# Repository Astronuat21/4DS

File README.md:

Hallo! Welcome to the Github Repository for the 4DS.

4DS is a solo project by Astronuat21 (me!!) aiming to make a dual screen console _akin to the Nintendo DS's_ but with stronger hardware, better battery life and specs in general. The device is also much larger than the ones you might have at home; coming in at around 19x11.5x3cm, the device is better suited for people with bigger hands who may find uncomfortability using even the stardard XL models. The hardware mostly tops the Switch, using the Lattepanda Mu SoC and it's N100 CPU, alongside 16GB of RAM and expandable Gen 3 SSD storage. If you so choose, this project should also be compatible with the upgraded N305 version (although it will be almost useless due to its higher PSU requirements). **NOTE: THIS WILL NOT WORK WITH THE LATTEPANDA MU ULTRA, SINCE IT USES 1.8V I2C and GPIOs.**

This repository contains all the PCB files used in this project, including schematics and circuit boards. **Assuming everything works,** you should be able to reproduce the exact boards I used and reprint them for yourself. Also included are all the 3D files used in 3D printing or other purposes as well as some *outdated -_-* images to look at. They can be found in **/3D Models** and **/Images** respectively. You will also need some of the additional programs included for things like the RP2354 Microcontroller, alongside some other helpful scripts, which can be found in **/Programs**.

I built this to challenge myself to make a console that I would be proud to daily drive. My 2DS XL is great, but it definitely can't play my Steam library, and while I _can_ fit a Switch in some pockets, it dosen't quite have the extensive game library (for what I actually play), the _New (or not really)_ DS in comparison can pretty much play everything before it aside from N64/Gamecube. The Switch needs Nintendo Online (yucky subscription), and that isn't even the full library anyways. 

I may make a v2 using the lattepanda mu ultra, but that thing is like $1000 so... anyone got spare cash?

If you intend to use this repository for any reason, **PLEASE CREDIT ME!!** I am happy to have others use this project as a reference or recreate what I have built, you can contact me with whatever you make, I would be honored. In the future, a _full-ish_ guide will be provided so that you can build your own 4DS if you'd like, but hopefully the repository is clear enough that you can do it on your own.

**DISCLAIMER (yap):** The 4DS and all its files is under the AGPL-3.0 license. I'm therefore technically allowing this repository to used for things like commercial purposes, but trust me, you really don't want to start using this repo just all on your own like that. My warning to you is that _many decisions made here were done from extensive research and considerations from dozens of specifications and datasheets, some areas of this design are much more sensitive than expected, and some areas are not._ I am happy to clarify certain things, but only if I believe your goal is actually good (aka, no AI slop). I'm giving this warning not because you must consult me, but if you choose not to, **find someone to wish you good luck. You're going to need it.**

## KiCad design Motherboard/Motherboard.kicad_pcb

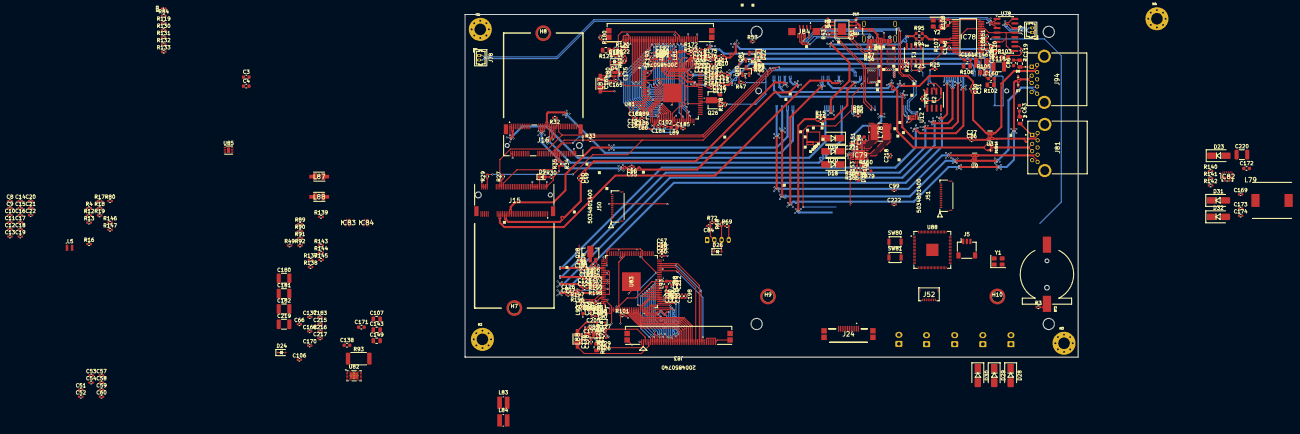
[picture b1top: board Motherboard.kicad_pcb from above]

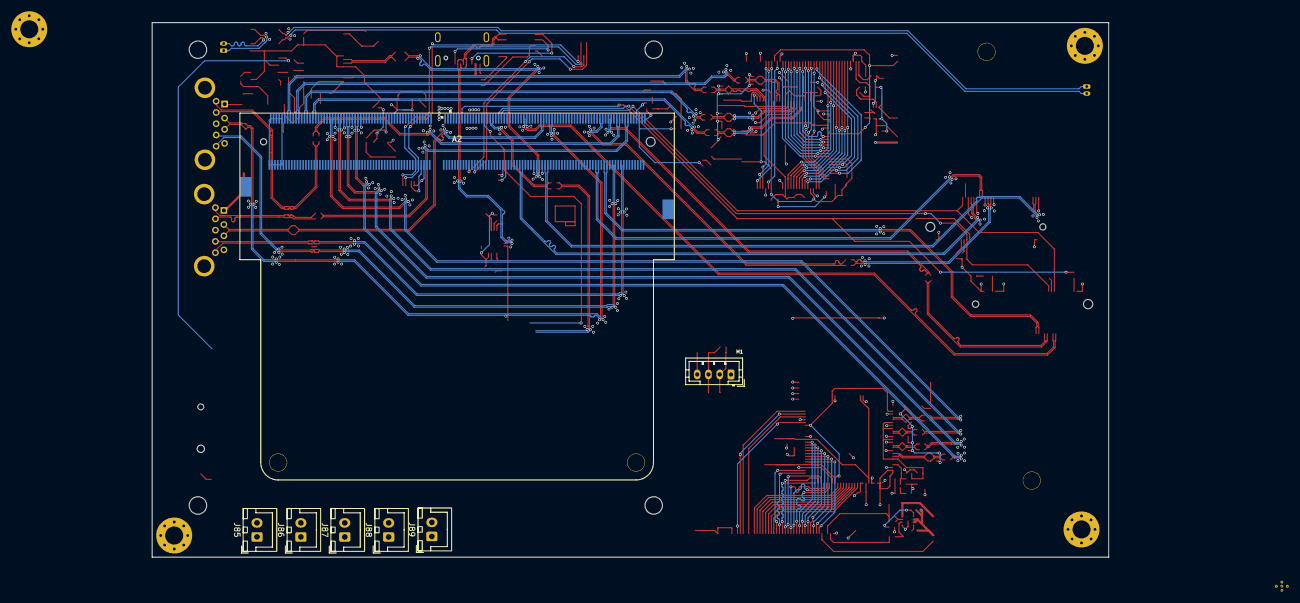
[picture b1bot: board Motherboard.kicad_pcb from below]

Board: 4 copper layers, 170.0 x 95.0 mm, 348 parts (7 on the bottom side), 317 nets.

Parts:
A2: LattePanda_Mu; LattePanda_Module_H8.0mm_Horizontal
BT2: Battery_Cell; Battery_Holder_CR1220_S8411-45R
C3, C4: 15pF; C_0603_1608Metric
C8, C9, C12, C13, C14, C15, C16, C17, C18, C20, C21, C26, C27, C30, C31, C52, C54, C58, C58#2, C60, C60#2, C84: 100nF; C_0402_1005Metric
C10, C11, C19, C22, C99: 4.7uF; C_0402_1005Metric
C49, C50, C55, C56, C169: 220nF; C_0402_1005Metric
C51, C53, C57, C57#2, C59, C59#2, C90, C102, C104, C106, C108, C110, C111, C112, C113, C114, C115, C116, C117, C121, C122, C123, C124, C125, C126, C127, C131, C150, C158, C164, C170, C177, C198, C207, C208, C215, C216, C217, C218, C221, C222: 10uF; C_0402_1005Metric
C61, C66, C119, C120, C128, C137, C147, C148, C151, C165, C166, C176, C179: 1uF; C_0402_1005Metric
C63, C86: 22uF; C_0603_1608Metric
C98: 47nF; C_0603_1608Metric
C107: 10uF; C_0805_2012Metric
C118, C146: 100uF; C_1210_3225Metric
C138: 0.47uF; C_0603_1608Metric
C143, C149: 22uF; C_0805_2012Metric
C160, C161: 0.022uF; C_0603_1608Metric
C168, C183: 1.2nF; C_0402_1005Metric
C171: 100nF; C_0603_1608Metric
C172: 2.2uF; C_0603_1608Metric
C173: 39nF; C_0402_1005Metric
C174: 91pF; C_0402_1005Metric
C175, C178: 10nF; C_0402_1005Metric
C180, C181, C182, C219, C220: 47uF; C_1210_3225Metric
C184, C185, C186, C187, C188, C189, C190, C191, C192, C193, C194, C195, C196, C197, C199, C200, C201, C202, C203, C204, C205, C206, C209, C210, C211, C212, C213, C214: 0.1uF; C_0402_1005Metric
D4, D5, D26: 1N5819WS; D_SOD-323
D7, D8, D10, D11, D15, D16, D21, D33: ESD5V0B03; D_0402_1005Metric
D9, D22, D25: LED_G; LED_0603_1608Metric
D12, D13, D14: PESD24VS1UL-N; D_0402_1005Metric
D18, D19, D20, D23, D28, D29, D30, D31, D32: SS54; D_SMA
D24: B5819WS-TP; D_SOD-323
E1, E2: 24AA025UIDT-I/SN; SOIC8-N_MC_MCH
F4, F6: 6V/2A; Fuse_0805_2012Metric
H1, H2, H3, H4: MountingHole_Pad; MountingHole_3.2mm_M3_Pad_Via
H7, H8: MountingHole_M2.0; MountingHole_3mm_M2_Pad_TopOnly
H9, H10: MountingHole_Pad; MountingHole_3mm_M2_Pad_TopOnly
IC78: PCM2704CDBR; SOP65P780X200-28N
IC79: BQ25606RGER; QFN50P400X400X100-25N-D
IC82: TPS61288LRQQR; PTPS61288RQQR
IC83, IC84: TPS62903RPJR
J5: SM03B-SRSS-TB; JST_SH_SM03B-SRSS-TB_1x03-1MP_P1.00mm_Horizontal
J15: M.2 Socket M; MDT420M03001
J16: M.2 Socket E; MDT420E03001
J24: 200485-0710; 2004850710
J50, J51: 5034801400
J52: 503480-0800; 5034800800
J78: Speaker_L; Molex_PicoBlade_53047-0210_1x02_P1.25mm_Vertical
J79: Speaker_R; Molex_PicoBlade_53047-0210_1x02_P1.25mm_Vertical
J80: USB_C_Receptacle_USB2.0_16P; USB_C_Receptacle_GCT_USB4105-xx-A_16P_TopMnt_Horizontal
J81, J94: GSB311A41EU
J83, J90: 2004850740; CON_2004850740
J84: FFC2A33-08-T-R; FFC2A3308TR
J85: JST_XHP2_Battery1; JST_XH_B2B-XH-A_1x02_P2.50mm_Vertical
J86: JST_XHP2_Battery2; JST_XH_B2B-XH-A_1x02_P2.50mm_Vertical
J87: JST_XHP2_Battery3; JST_XH_B2B-XH-A_1x02_P2.50mm_Vertical
J88: JST_XHP2_Battery4; JST_XH_B2B-XH-A_1x02_P2.50mm_Vertical
J89: JST_XHP2_Battery5; JST_XH_B2B-XH-A_1x02_P2.50mm_Vertical
L5: 3.3uH; L_pol_2016
L78: SRN5030HA-1R0Y; SRN5030HA1R0Y
L79: 7443330220; WE-HCC_109021
L81, L82, L86, L89, L90, L91, L92, L93: BLM18RK601SN1D; L_0603_1608Metric
L83, L84: 74438336010HT
L87, L87#2, L88, L88#2: LQH32CN220K23L; LQH32DN100K23L
M1: Fan_4pin; JST_PH_B4B-PH-K_1x04_P2.00mm_Vertical
Q26, Q28: 2SK3018-TP; SOT-89-3
Q80, Q81: 2N7002; SOT-23
R3, R12, R13, R16, R37, R47: 1k/1%; R_0402_1005Metric
R4, R18, R19, R22, R23, R24, R25, R34, R35, R36, R49, R85, R86, R91, R92, R100, R101, R154: 10k/1%; R_0402_1005Metric
R14, R15: 27R; R_0402_1005Metric
R17: 33R/1%; R_0402_1005Metric
R27, R29, R32, R33: 0R/1%; R_0402_1005Metric
R30, R52, R53, R155: 2.2k/1%; R_0402_1005Metric
R43: 6.8k/1%; R_0402_1005Metric
R46, R48, R69: 100R/1%; R_0402_1005Metric
R51, R80, R138, R144: 100k/1%; R_0402_1005Metric
R68: 21.5K/1%; R_0402_1005Metric
R72: 4.7K/1%; R_0402_1005Metric
R84, R119: 150R/1%; R_0402_1005Metric
R89, R90: 5.1k/1%; R_0402_1005Metric
R93: 0.010R/1%; R_2512_6332Metric
R94, R95: 22R/1%; R_0603_1608Metric
R102, R106: 16R/1%; R_0805_2012Metric
R103, R105: 330R/1%; R_0805_2012Metric
R107: 1.5k/1%; R_0805_2012Metric
R108: 1M/1%; R_0603_1608Metric
R120: 5.1R/1%; R_0402_1005Metric
R121, R122, R127, R128: 910k/1%; R_0402_1005Metric
R123, R126: 5k/1%; R_0402_1005Metric
R124, R125: 90.9k/1%; R_0805_2012Metric
R129: 10R/1%; R_0402_1005Metric
R130, R131, R132, R133: 47R/1%; R_0402_1005Metric
R137, R143: 40.2k/1%; R_0402_1005Metric
R139: 249k/1%; R_0402_1005Metric
R140: 39.2k/1%; R_0402_1005Metric
R141: 931k/1%; R_0402_1005Metric
R142: 48.7k/1%; R_0402_1005Metric
R145: 76.8k/1%; R_0402_1005Metric
R146, R147: 470R/1%; R_0402_1005Metric
R150: 30k/1%; R_0402_1005Metric
R151: 5.24k/1%; R_0402_1005Metric
R152: 226R/1%; R_0402_1005Metric
R153: 169R/1%; R_0402_1005Metric
R166, R167, R168, R169, R172, R173, R175, R176, R196, R197, R198, R199, R202, R203, R205, R206: 56k/1%; R_0402_1005Metric
R178, R208: 21.5k/1%; R_0402_1005Metric
SW80, SW81: SW_Push; SW_SPST_B3U-1000P
TH79: 10k/1%; R_0603_1608Metric
U3, U9, U12: D3V3XA4B10LP-7; Diodes_UDFN-10_1x2.5mm_P0.5mm
U14: CH224K; ESSOP-10-1EP_3.9x5mm_P1.0mm_EP3.2x2.3
U78: PAM8406D; SOIC-16_3.9x9.9mm_P1.27mm
U80, U85, U85#2: PAM2841G; DFN-8-1EP_2x2mm_P0.5mm_EP0.86x1.55mm
U81, U83: TFP401APZP; PZP100_5P2X5P2
U82: BQ27441DRZT-G1A; Texas_S-PDSO-N12
U88: RP2354B; QFN-80-1EP_10x10mm_P0.4mm_EP3.4x3.4mm
Y1, Y2: ABM8-272-T3; Crystal_SMD_3225-4Pin_3.2x2.5mm

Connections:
+1V1: C8.2, C9.2, C10.2, C22.1, L5.2, U88.10 (DVDD), U88.32 (DVDD), U88.51 (DVDD), U88.65 (VREG_FB)
+3V3: C12.2, C13.2, C14.2, C15.2, C16.2, C17.2, C18.2, C19.2, C20.2, C21.2, C51.2, C52.2, C53.2, C54.2, C57.2, C57#2.2, C58.2, C58#2.2, C59.2, C59#2.2, C60.2, C60#2.2, C143.1, C164.2, C165.2, C176.2, C177.2, D25.2 (A), E1.8, E2.8, IC78.7 (VDD), IC78.10 (VBUS), IC78.25 (TEST1), IC78.26 (TEST0), IC78.27 (~SSPND), IC83.3 (VOS), J15.2 (3.3V), J15.4 (3.3V), J15.12 (3.3V), J15.14 (3.3V), J15.16 (3.3V), J15.18 (3.3V), J15.70 (3.3V), J15.72 (3.3V), J15.74 (3.3V), J16.2 (3.3V), J16.4 (3.3V), J16.72 (3.3V), J16.74 (3.3V), J24.2, J50.3, J50.9, J51.3, J51.13, J83.4, J84.3, J90.4, L81.1, L82.1, L83.2, L86.1, L87.1, L87.3, L87#2.1, L87#2.3, L88.1, L88.3, L88#2.1, L88#2.3, L89.1, L90.1, L91.1, L92.1, L93.1, R17.2, R18.1, R19.2, R22.1, R23.2, R24.1, R25.2, R30.2, R34.2, R35.1, R52.2, R89.2, R90.2, R92.2, R100.1, R101.1, R107.1, R138.2, R146.1, R147.1, R154.2, U78.4 (PVDDL), U78.6 (VDD), U78.9 (MODE), U78.13 (PVDDR), U80.2 (VIN), U80.3 (ENA), U81.2 (*PD), U81.3 (ST), U81.7 (*STAG), U81.99 (RSVD), U81.100 (OCK_INV), U83.2 (*PD), U83.3 (ST), U83.7 (*STAG), U83.99 (RSVD), U83.100 (OCK_INV), U85.2 (VIN), U85.3 (ENA), U85#2.2 (VIN), U85#2.3 (ENA), U88.5 (IOVDD), U88.15 (IOVDD), U88.24 (IOVDD), U88.29 (IOVDD), U88.41 (IOVDD), U88.50 (IOVDD), U88.59 (ADC_AVDD), U88.60 (IOVDD), U88.64 (VREG_VIN), U88.68 (USB_OTP_VDD), U88.69 (QSPI_IOVDD), U88.76 (IOVDD)
+5V: C63.2, C84.1, C86.2, C149.1, D26.1 (K), F4.1, F6.1, IC84.3 (VOS), L84.2, M1.2 (+), R72.1, R144.2
+9V: D12.1 (K), D18.2 (A), D19.2 (A), D20.2 (A), J80.A4 (VBUS), J80.A9 (VBUS), J80.B4 (VBUS), J80.B9 (VBUS), R36.1, R37.1
+BATT: A2.115 (VBAT), R3.1
/EXIO/Col1: J50.5, U88.77 (GPIO0)
/EXIO/Col2: J50.11, U88.78 (GPIO1)
/EXIO/Col3: J51.11, U88.38 (GPIO30)
/EXIO/Col4: J51.9, U88.39 (GPIO31)
/EXIO/LED_PWR_B: R131.1, U88.20 (GPIO20)
/EXIO/LED_PWR_G: R132.1, U88.19 (GPIO19)
/EXIO/LED_PWR_R: R119.1, U88.18 (GPIO18)
/EXIO/LED_WiFi_B: R133.1, U88.17 (GPIO17)
/EXIO/LED_WiFi_G: R130.1, U88.16 (GPIO16)
/EXIO/LED_WiFi_R: R84.1, U88.14 (GPIO15)
/EXIO/L_ADC_X: J50.13, U88.52 (GPIO41/ADC1)
/EXIO/L_ADC_Y: J50.12, U88.49 (GPIO40/ADC0)
/EXIO/PWR_Button: D33.1 (A1), J52.1, Q80.1 (G)
/EXIO/RPi_HALL_L: J50.1, U88.80 (GPIO3)
/EXIO/RPi_HALL_R: J51.1, U88.40 (GPIO32)
/EXIO/R_ADC_X: J51.5, U88.54 (GPIO43/ADC3)
/EXIO/R_ADC_Y: J51.6, U88.55 (GPIO44/ADC4)
/EXIO/Row1: J50.4, J51.2, U88.2 (GPIO5)
/EXIO/Row2: J50.7, J51.7, U88.4 (GPIO7)
/EXIO/Row3: J50.2, J51.8, U88.1 (GPIO4)
/EXIO/Row4: J50.6, J51.12, U88.3 (GPIO6)
/EXIO/Row5: J50.14, J51.10, U88.6 (GPIO8)
/EXIO/SL_BRI: J51.14, U88.58 (GPIO47/ADC7)
/EXIO/SL_VOL: J50.8, U88.53 (GPIO42/ADC2)
/Fan_Temp/FAN_1_PWM: A2.2 (FAN1_PWM), R69.1
/Fan_Temp/FAN_1_TAC: A2.4 (FAN1_TAC), R68.2
/LattePanda Module/AMP_L: C120.1, U78.7 (INL)
/LattePanda Module/AMP_R: C119.1, U78.10 (INR)
/LattePanda Module/Audio_D+: A2.76 (USB2_P7+), R94.2
/LattePanda Module/Audio_D-: A2.78 (USB2_P7-), R95.1
/LattePanda Module/Audio_DX+: IC78.9 (D+), R94.1, R107.2
/LattePanda Module/Audio_DX-: IC78.8 (D-), R95.2
/LattePanda Module/DDIB_INT: A2.124 (GPP_F13), J24.9
/LattePanda Module/DDIB_RST: A2.120 (GPP_F15), J24.7
/LattePanda Module/DDIB_TOUCH_SCL: A2.150 (I2C3_SCL), J24.3, U12.5, U12.6 (NC)
/LattePanda Module/DDIB_TOUCH_SDA: A2.152 (I2C3_SDA), J24.5, U12.4, U12.7 (NC)
/LattePanda Module/DDIB_TX0+: A2.217 (DDIB_TX0+), C90.1
/LattePanda Module/DDIB_TX0-: A2.215 (DDIB_TX0-), C121.1
/LattePanda Module/DDIB_TX1+: A2.211 (DDIB_TX1+), C122.1
/LattePanda Module/DDIB_TX1-: A2.209 (DDIB_TX1-), C123.1
/LattePanda Module/DDIB_TX2+: A2.205 (DDIB_TX2+), C124.1
/LattePanda Module/DDIB_TX2-: A2.203 (DDIB_TX2-), C125.1
/LattePanda Module/DDIB_TX3+: A2.199 (DDIB_TX3+), C126.1
/LattePanda Module/DDIB_TX3-: A2.197 (DDIB_TX3-), C127.1
/LattePanda Module/HSIO_0_TX+: A2.13 (HSIO0_TX+), C27.1
/LattePanda Module/HSIO_0_TX-: A2.15 (HSIO0_TX-), C26.1
/LattePanda Module/HSIO_1_TX+: A2.19 (HSIO1_TX+), C31.1
/LattePanda Module/HSIO_1_TX-: A2.21 (HSIO1_TX-), C30.1
/LattePanda Module/HSIO_2_RX+: A2.28 (HSIO2_RX+), J15.43 (PERp0/SATA-B-)
/LattePanda Module/HSIO_2_RX-: A2.30 (HSIO2_RX-), J15.41 (PERn0/SATA-B+)
/LattePanda Module/HSIO_2_TX+: A2.25 (HSIO2_TX+), C49.1
/LattePanda Module/HSIO_2_TX-: A2.27 (HSIO2_TX-), C50.1
/LattePanda Module/HSIO_3_RX+: A2.34 (HSIO3_RX+), J16.41 (PERp0)
/LattePanda Module/HSIO_3_RX-: A2.36 (HSIO3_RX-), J16.43 (PERn0)
/LattePanda Module/HSIO_3_TX+: A2.31 (HSIO3_TX+), C55.1
/LattePanda Module/HSIO_3_TX-: A2.33 (HSIO3_TX-), C56.1
/LattePanda Module/LOUT+: J78.1, U78.1 (+OUT_L)
/LattePanda Module/LOUT-: J78.2, U78.3 (-OUT_L)
/LattePanda Module/REFCLK0+: A2.85 (REFCLK0+), J15.53 (REFCLKn)
/LattePanda Module/REFCLK0-: A2.87 (REFCLK0-), J15.55 (REFCLKp)
/LattePanda Module/REFCLK3+: A2.88 (REFCLK3+), J16.47 (REFCLKp0)
/LattePanda Module/REFCLK3-: A2.90 (REFCLK3-), J16.49 (REFCLKn0)
/LattePanda Module/ROUT+: J79.1, U78.16 (+OUT_R)
/LattePanda Module/ROUT-: J79.2, U78.14 (-OUT_R)
/LattePanda Module/RP+: R14.1, U88.66 (USB_DM)
/LattePanda Module/RP-: R15.1, U88.67 (USB_DP)
/LattePanda Module/RPI_BAT_GPO: A2.118 (GPP_F16), R92.1, U82.12 (GPOUT)
/LattePanda Module/RPI_BAT_SCL: A2.146 (I2C4_SCL), R89.1, U82.1 (SDA)
/LattePanda Module/RPI_BAT_SDA: A2.148 (I2C4_SDA), R90.1, U82.2 (SCL)
/LattePanda Module/RPI_BAT_STAT: IC79.5 (STAT), R154.1, R155.2, U88.46 (GPIO37)
/LattePanda Module/RPR+: A2.111 (USB2_P5+), R14.2
/LattePanda Module/RPR-: A2.109 (USB2_P5-), R15.2
/LattePanda Module/RPi_5A_SCL: R19.1, U88.44 (GPIO35)
/LattePanda Module/RPi_5A_SDA: R18.2, U88.43 (GPIO34)
/LattePanda Module/RPi_LCD_EN: J83.31, J90.31, R100.2, R101.2, U81.8 (SCDT), U81.9 (*PDO), U83.8 (SCDT), U83.9 (*PDO), U88.79 (GPIO2)
/LattePanda Module/RPi_PAM_LPWR: U78.5 (~MUTE), U88.25 (GPIO24)
/LattePanda Module/SLS_S3: A2.7 (SLS_S3), R46.1, U88.36 (GPIO28)
/LattePanda Module/SUSCLK_WIFI: A2.131 (SUSCLK), R29.2, R33.2
/LattePanda Module/SWCLK: J5.1, U88.33 (SWCLK)
/LattePanda Module/SWD: J5.3, U88.34 (SWDIO)
/LattePanda Module/TCP0_INT: A2.126 (GPP_F12), J84.6
/LattePanda Module/TCP0_RST: A2.122 (GPP_F14), J84.7
/LattePanda Module/TCP0_TOUCH_SCL: A2.154 (I2C2_SCL), J84.4, U12.2, U12.9 (NC)
/LattePanda Module/TCP0_TOUCH_SDA: A2.156 (I2C2_SDA), J84.5, U12.1, U12.10 (NC)
/LattePanda Module/TCP0_TX0+: A2.247 (TCP0_TX0+), C110.1
/LattePanda Module/TCP0_TX0-: A2.245 (TCP0_TX0-), C111.1
/LattePanda Module/TCP0_TX1+: A2.241 (TCP0_TXRX0+), C112.1
/LattePanda Module/TCP0_TX1-: A2.239 (TCP0_TXRX0-), C113.1
/LattePanda Module/TCP0_TX2+: A2.235 (TCP0_TX1+), C114.1
/LattePanda Module/TCP0_TX2-: A2.233 (TCP0_TX1-), C115.1
/LattePanda Module/TCP0_TX3+: A2.229 (TCP0_TXRX1+), C116.1
/LattePanda Module/TCP0_TX3-: A2.227 (TCP0_TXRX1-), C117.1
/LattePanda Module/USB_2_P7+: A2.70 (USB2_P4+), J16.3 (USB_D+)
/LattePanda Module/USB_2_P7-: A2.72 (USB2_P4-), J16.5 (USB_D-)
/LattePanda Module/WiFi_M2E_LED: J16.6 (~LED_1), U88.56 (GPIO45/ADC5)
/LattePanda Module/~PWR_SW: A2.1 (~PWRBTN), R48.2
/LattePanda Module/~USB_BOOT: R16.1, SW81.1
/M.2 E&M Key/CON_PCIE_TX_0+: C55.2, J16.35 (PETp0)
/M.2 E&M Key/CON_PCIE_TX_0-: C56.2, J16.37 (PETn0)
/M.2 E&M Key/CON_PCIE_TX_1+: C49.2, J15.49 (PETp0/SATA-A+)
/M.2 E&M Key/CON_PCIE_TX_1-: C50.2, J15.47 (PETn0/SATA-A-)
/M.2 E&M Key/~CLKREQE: J16.53 (~CLKREQ0), R32.1
/M.2 E&M Key/~CLKREQM: J15.52 (~CLKREQ), R27.1
/PSU/12VIn: C220.2, D23.2 (A), D31.2 (A), D32.2 (A), IC82.5 (VOUT), IC82.13 (VOUT), R141.2
/PSU/BAT+: C222.1, D28.1 (K), D29.1 (K), D30.1 (K), IC79.13 (BAT_1), IC79.14 (BAT_2)
/PSU/B_RAW: C137.2, J85.2, J86.2, J87.2, J88.2, J89.2, R93.2, U82.6 (BAT), U82.8 (SRP)
/PSU/CC1: D13.1 (K), J80.A5 (CC1), U14.7 (CC1)
/PSU/CC2: D14.1 (K), J80.B5 (CC2), U14.6 (CC2)
/PSU/PWR_C_D+: D11.2 (A2), IC79.3 (D+), J80.A6 (D+), J80.B6 (D+), U14.4 (DP)
/PSU/PWR_C_D-: D10.2 (A2), IC79.4 (D-), J80.A7 (D-), J80.B7 (D-), U14.5 (DM)
/PSU/SYS: C106.1, C170.1, C171.2, C215.1, C216.1, C217.1, C218.1, IC79.15 (SYS_1), IC79.16 (SYS_2), IC82.6 (EN), IC82.7 (VIN), IC82.14 (VIN), IC83.5 (EN), IC83.6 (VIN), L78.2, L79.1
/RGB/B0: J83.5, U83.30 (QE16)
/RGB/B1: J83.6, U83.31 (QE17)
/RGB/B2: J83.7, U83.32 (QE18)
/RGB/B3: J83.8, U83.33 (QE19)
/RGB/B4: J83.9, U83.34 (QE20)
/RGB/B5: J83.10, U83.35 (QE21)
/RGB/B6: J83.11, U83.36 (QE22)
/RGB/B7: J83.12, U83.37 (QE23)
/RGB/B8: J83.13, U83.20 (QE8)
/RGB/B9: J83.14, U83.21 (QE9)
/RGB/B10: J83.15, U83.22 (QE10)
/RGB/B11: J83.16, U83.23 (QE11)
/RGB/B12: J83.17, U83.24 (QE12)
/RGB/B13: J83.18, U83.25 (QE13)
/RGB/B14: J83.19, U83.26 (QE14)
/RGB/B15: J83.20, U83.27 (QE15)
/RGB/B16: J83.21, U83.10 (QE0)
/RGB/B17: J83.22, U83.11 (QE1)
/RGB/B18: J83.23, U83.12 (QE2)
/RGB/B19: J83.24, U83.13 (QE3)
/RGB/B20: J83.25, U83.14 (QE4)
/RGB/B21: J83.26, U83.15 (QE5)
/RGB/B22: J83.27, U83.16 (QE6)
/RGB/B23: J83.28, U83.17 (QE7)
/RGB/B-AVDD: C207.2, C209.1, C211.1, C213.1, C214.1, L92.2, U83.82 (AVDD), U83.84 (AVDD), U83.88 (AVDD), U83.95 (AVDD)
/RGB/B-DE: J83.30, U83.46 (DE)
/RGB/B-DVDD: C208.2, C210.1, C212.1, L93.2, U83.6 (DVDD), U83.38 (DVDD), U83.67 (DVDD)
/RGB/B-HS: J83.32, U83.48 (HSYNC)
/RGB/B-OVDD: C198.2, C200.1, C202.1, C204.1, C206.1, L91.2, U83.18 (OVDD), U83.29 (OVDD), U83.43 (OVDD), U83.57 (OVDD), U83.78 (OVDD)
/RGB/B-PCK: J83.34, U83.44 (ODCK)
/RGB/B-PVDD: C158.2, C199.1, C201.1, C203.1, C205.1, L90.2, U83.97 (PVDD)
/RGB/B-VS: J83.33, U83.47 (VSYNC)
/RGB/DDIB_CK+: C126.2, R197.1, U83.93 (RXC+)
/RGB/DDIB_CK-: C127.2, R196.1, U83.94 (RXC-)
/RGB/DDIB_D0+: C124.2, R199.1, U83.90 (RX0+)
/RGB/DDIB_D0-: C125.2, R198.1, U83.91 (RX0-)
/RGB/DDIB_D1+: C122.2, R203.1, U83.85 (RX1+)
/RGB/DDIB_D1-: C123.2, R202.1, U83.86 (RX1-)
/RGB/DDIB_D2+: C90.2, R206.1, U83.80 (RX2+)
/RGB/DDIB_D2-: C121.2, R205.1, U83.81 (RX2-)
/RGB/P0: J90.5, U81.30 (QE16)
/RGB/P1: J90.6, U81.31 (QE17)
/RGB/P2: J90.7, U81.32 (QE18)
/RGB/P3: J90.8, U81.33 (QE19)
/RGB/P4: J90.9, U81.34 (QE20)
/RGB/P5: J90.10, U81.35 (QE21)
/RGB/P6: J90.11, U81.36 (QE22)
/RGB/P7: J90.12, U81.37 (QE23)
/RGB/P8: J90.13, U81.20 (QE8)
/RGB/P9: J90.14, U81.21 (QE9)
/RGB/P10: J90.15, U81.22 (QE10)
/RGB/P11: J90.16, U81.23 (QE11)
/RGB/P12: J90.17, U81.24 (QE12)
/RGB/P13: J90.18, U81.25 (QE13)
/RGB/P14: J90.19, U81.26 (QE14)
/RGB/P15: J90.20, U81.27 (QE15)
/RGB/P16: J90.21, U81.10 (QE0)
/RGB/P17: J90.22, U81.11 (QE1)
/RGB/P18: J90.23, U81.12 (QE2)
/RGB/P19: J90.24, U81.13 (QE3)
/RGB/P20: J90.25, U81.14 (QE4)
/RGB/P21: J90.26, U81.15 (QE5)
/RGB/P22: J90.27, U81.16 (QE6)
/RGB/P23: J90.28, U81.17 (QE7)
/RGB/P-AVDD: C131.2, C194.1, C195.1, C196.1, C197.1, L81.2, U81.82 (AVDD), U81.84 (AVDD), U81.88 (AVDD), U81.95 (AVDD)
/RGB/P-DE: J90.34, U81.46 (DE)
/RGB/P-DVDD: C102.2, C184.1, C185.1, L89.2, U81.6 (DVDD), U81.38 (DVDD), U81.67 (DVDD)
/RGB/P-HS: J90.32, U81.48 (HSYNC)
/RGB/P-OVDD: C104.2, C186.1, C187.1, C188.1, C189.1, L86.2, U81.18 (OVDD), U81.29 (OVDD), U81.43 (OVDD), U81.57 (OVDD), U81.78 (OVDD)
/RGB/P-PCK: J90.30, U81.44 (ODCK)
/RGB/P-PVDD: C108.2, C190.1, C191.1, C192.1, C193.1, L82.2, U81.97 (PVDD)
/RGB/P-VS: J90.33, U81.47 (VSYNC)
/RGB/TMDS_CK+: C116.2, R167.1, U81.93 (RXC+)
/RGB/TMDS_CK-: C117.2, R166.1, U81.94 (RXC-)
/RGB/TMDS_D0+: C114.2, R169.1, U81.90 (RX0+)
/RGB/TMDS_D0-: C115.2, R168.1, U81.91 (RX0-)
/RGB/TMDS_D1+: C112.2, R173.1, U81.85 (RX1+)
/RGB/TMDS_D1-: C113.2, R172.1, U81.86 (RX1-)
/RGB/TMDS_D2+: C110.2, R176.1, U81.80 (RX2+)
/RGB/TMDS_D2-: C111.2, R175.1, U81.81 (RX2-)
/USB/CON_USB3_D_N: A2.73 (USB2_P2-), D16.2 (A2), J81.2 (D-)
/USB/CON_USB3_D_P: A2.75 (USB2_P2+), D15.2 (A2), J81.3 (D+)
/USB/CON_USB3_SSRX_N: A2.18 (HSIO0_RX-), J81.5 (STDA_SSRX-), U9.4, U9.7 (NC)
/USB/CON_USB3_SSRX_P: A2.16 (HSIO0_RX+), J81.6 (STDA_SSRX+), U9.5, U9.6 (NC)
/USB/CON_USB3_SSTX_N: C26.2, J81.8 (STDA_SSTX-), U3.1, U3.10 (NC)
/USB/CON_USB3_SSTX_P: C27.2, J81.9 (STDA_SSTX+), U3.2, U3.9 (NC)
/USB/CON_USB4_D_N: A2.67 (USB2_P1-), D8.2 (A2), J94.2 (D-)
/USB/CON_USB4_D_P: A2.69 (USB2_P1+), D7.2 (A2), J94.3 (D+)
/USB/CON_USB4_SSRX_N: A2.24 (HSIO1_RX-), J94.5 (STDA_SSRX-), U9.1, U9.10 (NC)
/USB/CON_USB4_SSRX_P: A2.22 (HSIO1_RX+), J94.6 (STDA_SSRX+), U9.2, U9.9 (NC)
/USB/CON_USB4_SSTX_N: C30.2, J94.8 (STDA_SSTX-), U3.4, U3.7 (NC)
/USB/CON_USB4_SSTX_P: C31.2, J94.9 (STDA_SSTX+), U3.5, U3.6 (NC)
/~PLT_RST: A2.105 (~PLTRST), J15.50 (~PERST), J16.52 (~PERST0)
/~PWR_LED/~PSON: A2.5 (SLS_S0), R47.1, R178.1, R208.1, U88.37 (GPIO29)
/~WAKE: A2.103 (~WAKE), J15.54 (~PEWAKE), J16.55 (~PEWAKE0)
GND: A2.11 (GND), A2.14 (GND), A2.17 (GND), A2.20 (GND), A2.23 (GND), A2.26 (GND), A2.29 (GND), A2.32 (GND), A2.35 (GND), A2.38 (GND), A2.41 (GND), A2.44 (GND), A2.47 (GND), A2.50 (GND), A2.53 (GND), A2.56 (GND), A2.59 (GND), A2.62 (GND), A2.65 (GND), A2.68 (GND), A2.71 (GND), A2.74 (GND), A2.77 (GND), A2.80 (GND), A2.83 (GND), A2.86 (GND), A2.89 (GND), A2.92 (GND), A2.95 (GND), A2.98 (GND), A2.101 (GND), A2.107 (GND), A2.110 (GND), A2.113 (GND), A2.116 (GND), A2.135 (GND), A2.136 (GND), A2.151 (GND), A2.158 (GND), A2.167 (GND), A2.170 (GND), A2.181 (GND), A2.182 (GND), A2.188 (GND), A2.189 (GND), A2.194 (GND), A2.195 (GND), A2.200 (GND), A2.201 (GND), A2.206 (GND), A2.207 (GND), A2.212 (GND), A2.213 (GND), A2.218 (GND), A2.219 (GND), A2.224 (GND), A2.225 (GND), A2.230 (GND), A2.231 (GND), A2.236 (GND), A2.237 (GND), A2.242 (GND), A2.243 (GND), A2.248 (GND), A2.249 (GND), A2.MP (Mountinge_Pads), BT2.2 (-), C3.1, C4.1, C8.1, C9.1, C10.1, C11.1, C12.1, C13.1, C14.1, C15.1, C16.1, C17.1, C18.1, C19.1, C20.1, C21.1, C22.2, C51.1, C52.1, C53.1, C54.1, C57.1, C57#2.1, C58.1, C58#2.1, C59.1, C59#2.1, C60.1, C60#2.1, C61.2, C63.1, C66.2, C84.2, C86.1, C99.2, C102.1, C104.1, C106.2, C107.2, C108.1, C128.1, C131.1, C137.1, C138.1, C143.2, C147.2, C148.2, C150.2, C151.2, C158.1, C165.1, C168.1, C170.2, C171.1, C172.2, C173.1, C174.1, C175.1, C176.1, C178.1, C180.1, C181.1, C182.1, C183.1, C184.2, C185.2, C186.2, C187.2, C188.2, C189.2, C190.2, C191.2, C192.2, C193.2, C194.2, C195.2, C196.2, C197.2, C198.1, C199.2, C200.2, C201.2, C202.2, C203.2, C204.2, C205.2, C206.2, C207.1, C208.1, C209.2, C210.2, C211.2, C212.2, C213.2, C214.2, C215.2, C216.2, C217.2, C218.2, C219.1, C220.1, C221.2, C222.2, D7.1 (A1), D8.1 (A1), D10.1 (A1), D11.1 (A1), D12.2 (A), D13.2 (A), D14.2 (A), D15.1 (A1), D16.1 (A1), D21.1 (A1), D24.2 (A), D33.2 (A2), E1.1, E1.2, E1.3, E1.4, E2.1, E2.2, E2.3, E2.4, H1.1 (1_1), H2.1 (1_1), H3.1 (1_1), H4.1 (1_1), H7.1 (1_1), H8.1 (1_1), H9.1 (1_1), H10.1 (1_1), IC78.4 (PSEL), IC78.6 (DGND), IC78.11 (ZGND), IC78.12 (AGNDL), IC78.17 (AGNDR), IC78.19 (PGND), IC78.21 (HOST), IC78.22 (HID0/MS), IC78.23 (HID1/MC), IC78.24 (HID2/MD), IC79.6 (OTG), IC79.9 (~CE), IC79.17 (GND_1), IC79.18 (GND_2), IC79.25 (EP), IC82.3 (PGND), IC82.10 (AGND), IC82.12 (PGND), IC83.4 (GND), IC84.4 (GND), J5.2, J5.MP (MountPin), J15.1 (GND), J15.3 (GND), J15.9 (GND), J15.15 (GND), J15.21 (GND), J15.27 (GND), J15.33 (GND), J15.39 (GND), J15.45 (GND), J15.51 (GND), J15.57 (GND), J15.71 (GND), J15.73 (GND), J15.75 (GND), J15.MP1, J15.MP2, J16.1 (GND), J16.7 (GND), J16.18 (GND), J16.33 (GND), J16.39 (GND), J16.45 (GND), J16.51 (GND), J16.57 (GND), J16.63 (GND), J16.69 (GND), J16.75 (GND), J16.MP1, J16.MP2, J24.1, J24.10, J24.G1 (GND_1), J24.G2 (GND_2), J24.MP1, J24.MP2, J24.MP3, J24.MP4, J50.10, J50.P1, J50.P2, J51.4, J51.P1, J51.P2, J52.2, J52.9, J52.10, J80.A1 (GND), J80.A12 (GND), J80.B1 (GND), J80.B12 (GND), J80.SH (SHIELD), J81.4 (GND), J81.7 (GND_DRAIN), J81.MH1, J81.MH2, J83.3, J83.29, J83.36, J83.G1, J83.G2, J83.P1, J83.P2, J83.P3, J83.P4, J84.1, J84.8, J84.MP1, J84.MP2, J85.1, J86.1, J87.1, J88.1, J89.1, J90.3, J90.29, J90.36, J90.G1, J90.G2, J90.P1, J90.P2, J90.P3, J90.P4, J94.4 (GND), J94.7 (GND_DRAIN), J94.MH1, J94.MH2, M1.1 (-), Q26.2 (S), Q28.2 (S), Q80.2 (S), Q81.2 (S), R13.1, R27.2, R32.2, R43.2, R49.1, R51.1, R80.2, R85.2, R86.2, R91.1, R102.2, R103.1, R105.1, R106.2, R120.1, R122.1, R124.2, R125.2, R128.1, R129.1, R137.2, R139.1, R142.1, R143.2, R150.2, R152.2, R153.1, SW81.2, TH79.1, U3.3 (VSS), U3.8 (VSS), U9.3 (VSS), U9.8 (VSS), U12.3 (VSS), U12.8 (VSS), U14.0 (GND), U78.2 (PGNDL), U78.11 (GND), U78.15 (PGNDR), U80.5 (GND), U80.9 (GND), U81.1 (DFO), U81.4 (PIXS), U81.5 (GND), U81.19 (OGND), U81.28 (OGND), U81.39 (GND), U81.45 (OGND), U81.58 (OGND), U81.68 (GND), U81.76 (OGND), U81.79 (AGND), U81.83 (AGND), U81.87 (AGND), U81.89 (AGND), U81.92 (AGND), U81.98 (PGND), U81.PAD, U82.3 (V_{SS}), U82.13 (PAD), U83.1 (DFO), U83.4 (PIXS), U83.5 (GND), U83.19 (OGND), U83.28 (OGND), U83.39 (GND), U83.45 (OGND), U83.58 (OGND), U83.68 (GND), U83.76 (OGND), U83.79 (AGND), U83.83 (AGND), U83.87 (AGND), U83.89 (AGND), U83.92 (AGND), U83.98 (PGND), U83.PAD, U85.5 (GND), U85.9 (GND), U85#2.5 (GND), U85#2.9 (GND), U88.62 (VREG_PGND)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
LED_SCB+: C179.2, D5.1 (K), J83.2, R127.2
LED_SCB-: J83.1, R126.1, R129.2
LED_SCT+: C166.2, D4.1 (K), J90.2, R121.2
LED_SCT-: J90.1, R120.2, R123.1
unnamed: A2.171 (DDIB_DDC_SCL), E1.6, R23.1
unnamed: A2.169 (DDIB_DDC_SDA), E1.5, R22.2
unnamed: A2.183 (DDIB_HPD), R147.2
unnamed: A2.179 (TCP0_DDC_SCL), E2.6, R25.1
unnamed: A2.177 (TCP0_DDC_SDA), E2.5, R24.2
unnamed: A2.187 (TCP0_HPD), R146.2
unnamed: A2.185 (TCP1_HPD), R80.1
unnamed: A2.133 (~BIOS_SEL), R4.1
unnamed: A2.100 (~CLKREQ3), R86.1
unnamed: A2.102 (~CLKREQ4), R85.1
unnamed: BT2.1 (+), R3.2
unnamed: C4.2, R12.1, Y1.3
unnamed: C118.2, C119.2, R103.2
unnamed: C120.2, C146.2, R105.2
unnamed: C149.2, R145.1
unnamed: C160.2, R102.1
unnamed: C161.2, R106.1
unnamed: C169.2, IC82.4 (SW), IC82.9 (SW), L79.2
unnamed: C173.2, R140.2
unnamed: D4.2 (A), L87.2, L87.4, L87#2.2, L87#2.4, U80.8 (SW)
unnamed: D5.2 (A), L88.2, L88.4, L88#2.2, L88#2.4, U85.8 (SW), U85#2.8 (SW)
unnamed: D9.2 (A), R30.1
unnamed: D9.1 (K), J15.10 (DAS/~DSS/~LED1)
unnamed: D18.1 (K), D19.1 (K), D20.1 (K), IC79.1 (VAC), IC79.24 (VBUS)
unnamed: D22.2 (A), R52.1
unnamed: D22.1 (K), Q81.3 (D)
unnamed: D25.1 (K), R155.1
unnamed: D26.2 (A), M1.3 (Tacho), R68.1, R72.2
unnamed: D28.2 (A), D29.2 (A), D30.2 (A), R93.1, U82.7 (SRN)
unnamed: C148.1, IC78.13 (VCCL)
unnamed: C151.1, IC78.20 (VCCP)
unnamed: C147.1, IC78.16 (VCCR)
unnamed: C150.1, IC78.18 (VCOM)
unnamed: C146.1, C161.1, IC78.14 (VOUTL)
unnamed: C118.1, C160.1, IC78.15 (VOUTR)
unnamed: IC78.28 (XTI), R108.2, Y2.1
unnamed: IC78.1 (XTO), R108.1, Y2.3
unnamed: C98.2, IC79.21 (BTST)
unnamed: IC79.10 (ICHG), R152.1
unnamed: IC79.8 (ILIM), R153.2
unnamed: C221.1, IC79.23 (PMID)
unnamed: C99.1, IC79.22 (REGN), R151.1
unnamed: C98.1, IC79.19 (SW_1), IC79.20 (SW_2), L78.1
unnamed: IC79.11 (TS), R150.1, R151.2, TH79.2
unnamed: C169.1, IC82.8 (BST)
unnamed: C174.2, IC82.2 (COMP), R140.1
unnamed: IC82.1 (FB), IC82.15 (FB), R141.1, R142.2
unnamed: C172.1, IC82.11 (VCC)
unnamed: IC83.9 (FB/VSET), R139.2
unnamed: IC83.7 (MODE/S-CONF), R137.1
unnamed: IC83.1 (PG), R138.1
unnamed: C168.2, IC83.8 (SS/TR)
unnamed: IC83.2 (SW), L83.1
unnamed: IC84.9 (FB/VSET), R145.2
unnamed: IC84.7 (MODE/S-CONF), R143.1
unnamed: IC84.1 (PG), R144.1
unnamed: C183.2, IC84.8 (SS/TR)
unnamed: IC84.2 (SW), L84.1
unnamed: J15.68 (SUSCLK), R29.1
unnamed: J16.50 (SUSCLK), R33.1
unnamed: J16.56 (~W_DISABLE1), R34.1
unnamed: J16.54 (~W_DISABLE2), R35.2
unnamed: J52.3, R84.2
unnamed: J52.4, R130.2
unnamed: J52.5, R133.2
unnamed: J52.6, R119.2
unnamed: J52.7, R132.2
unnamed: J52.8, R131.2
unnamed: F4.2, J81.1 (VBUS)
unnamed: F6.2, J94.1 (VBUS)
unnamed: M1.4 (PWM), R69.2
unnamed: Q26.3 (D), R166.2, R167.2, R168.2, R169.2, R172.2, R173.2, R175.2, R176.2
unnamed: Q26.1 (G), R178.2
unnamed: Q28.3 (D), R196.2, R197.2, R198.2, R199.2, R202.2, R203.2, R205.2, R206.2
unnamed: Q28.1 (G), R208.2
unnamed: Q81.1 (G), R47.2, R49.2
unnamed: R13.2, SW80.1
unnamed: R46.2, R51.2
unnamed: R43.1, U14.9 (CFG1)
unnamed: R36.2, U14.8 (VBUS)
unnamed: C61.1, R37.2, U14.1 (VDD)
unnamed: C128.2, U78.8 (VREF)
unnamed: C175.2, U80.4 (Comp)
unnamed: R123.2, R124.1, U80.6 (FB)
unnamed: R121.1, R122.2, U80.7 (OVP)
unnamed: R91.2, U82.10 (BIN)
unnamed: C138.2, U82.5 (V_{DD})
unnamed: C178.2, U85.4 (Comp), U85#2.4 (Comp)
unnamed: R125.1, R126.2, U85.6 (FB), U85#2.6 (FB)
unnamed: R127.1, R128.2, U85.7 (OVP), U85#2.7 (OVP)
unnamed: SW80.2, U88.35 (RUN)
unnamed: C11.2, R17.1, U88.61 (VREG_AVDD)
unnamed: L5.1, U88.63 (VREG_LX)
unnamed: C3.2, U88.30 (XIN), Y1.1
unnamed: R12.2, U88.31 (XOUT)
unnamed: R16.2, U88.75 (~QSPI_SS)
PGND_B: C177.1, C179.1, U85.1 (PGND), U85#2.1 (PGND)
PGND_T: C164.1, C166.1, U80.1 (PGND)
PWR: C66.1, D21.2 (A2), Q80.3 (D), R48.1
VDC: A2.250 (VIN), A2.251 (VIN), A2.252 (VIN), A2.253 (VIN), A2.254 (VIN), A2.255 (VIN), A2.256 (VIN), A2.257 (VIN), A2.258 (VIN), A2.259 (VIN), A2.260 (VIN), C107.1, C180.2, C181.2, C182.2, C219.2, D23.1 (K), D31.1 (K), D32.1 (K), IC84.5 (EN), IC84.6 (VIN), R53.1
VPullup: D24.1 (K), R4.2, R53.2

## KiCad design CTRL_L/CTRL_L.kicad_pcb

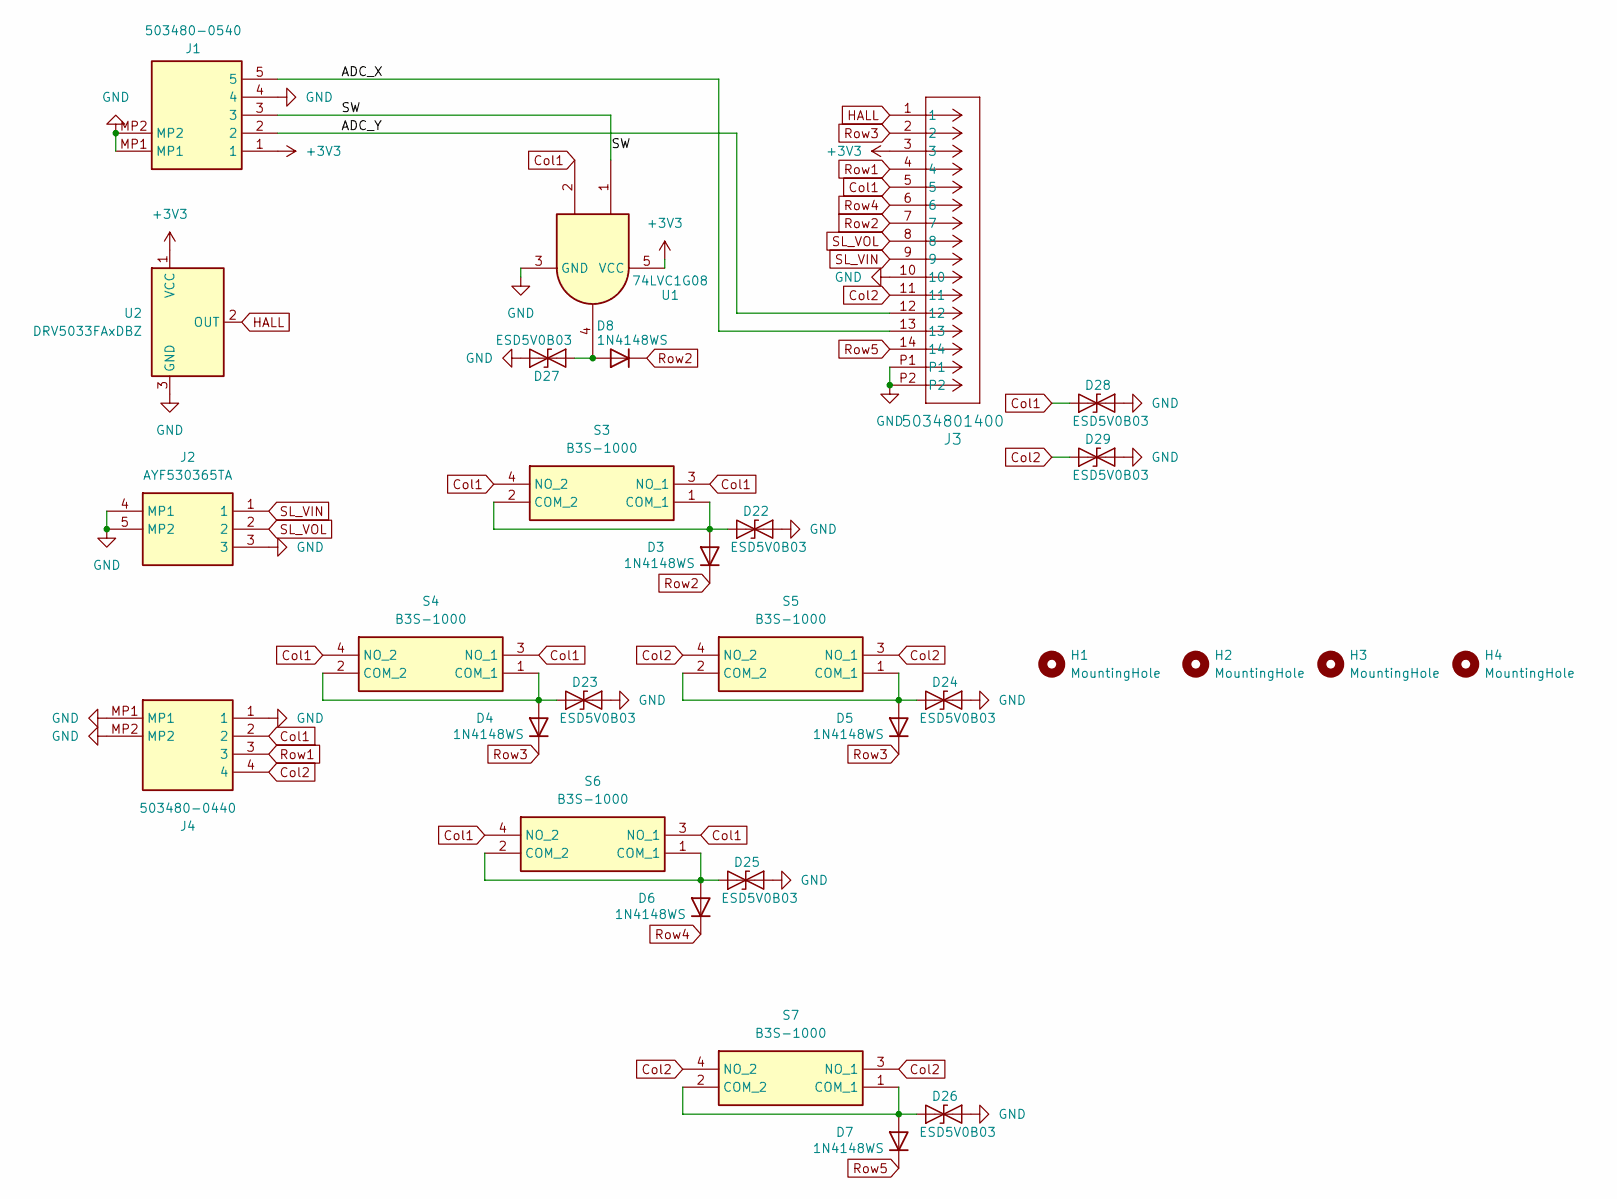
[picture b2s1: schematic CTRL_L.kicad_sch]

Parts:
D3, D4, D5, D6, D7, D8: 1N4148WS; D_SOD-323; MPN 1N4148WS; LCSC Part C917117
D22, D23, D24, D25, D26, D27, D28, D29: ESD5V0B03; D_0402_1005Metric; MPN ESD5V0B03-1006; LCSC Part C521894
H1, H2, H3, H4: MountingHole; MountingHole_2.7mm_M2.5; LCSC Part N/A
J1: 503480-0540; 5034800540; Mouser Part Number 538-503480-0540
J2: AYF530365TA; AYF530365T; Mouser Part Number 667-AYF530365TA
J3: 5034801400; MPN 5034801400; LCSC Part C505360
J4: 503480-0440; 5034800440; Mouser Part Number 538-503480-0440
S3, S4, S5, S6, S7: B3S-1000; B3S1000; Mouser Part Number 653-B3S-1000
U1: 74LVC1G08; SOT-23-5; MPN 74LVC1G08GV; LCSC Part C53185136
U2: DRV5033FAxDBZ; SOT-23; MPN DRV5033FAQDBZR; LCSC Part C2869057

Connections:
+3V3: J1.1, J3.3, U1.5 (VCC), U2.1 (VCC)
/ADC_X: J1.5, J3.13
/ADC_Y: J1.2, J3.12
/SW: J1.3, U1.1
Col1: D28.2 (A2), J3.5, J4.2, S3.3 (NO_1), S3.4 (NO_2), S4.3 (NO_1), S4.4 (NO_2), S6.3 (NO_1), S6.4 (NO_2), U1.2
Col2: D29.2 (A2), J3.11, J4.4, S5.3 (NO_1), S5.4 (NO_2), S7.3 (NO_1), S7.4 (NO_2)
GND: D22.1 (A1), D23.1 (A1), D24.1 (A1), D25.1 (A1), D26.1 (A1), D27.1 (A1), D28.1 (A1), D29.1 (A1), J1.4, J1.MP1, J1.MP2, J2.3, J2.4 (MP1), J2.5 (MP2), J3.10, J3.P1, J3.P2, J4.1, J4.MP1, J4.MP2, U1.3 (GND), U2.3 (GND)
HALL: J3.1, U2.2 (OUT)
unnamed: D3.2 (A), D22.2 (A2), S3.1 (COM_1), S3.2 (COM_2)
unnamed: D4.2 (A), D23.2 (A2), S4.1 (COM_1), S4.2 (COM_2)
unnamed: D5.2 (A), D24.2 (A2), S5.1 (COM_1), S5.2 (COM_2)
unnamed: D6.2 (A), D25.2 (A2), S6.1 (COM_1), S6.2 (COM_2)
unnamed: D7.2 (A), D26.2 (A2), S7.1 (COM_1), S7.2 (COM_2)
unnamed: D8.2 (A), D27.2 (A2), U1.4
Row1: J3.4, J4.3
Row2: D3.1 (K), D8.1 (K), J3.7
Row3: D4.1 (K), D5.1 (K), J3.2
Row4: D6.1 (K), J3.6
Row5: D7.1 (K), J3.14
SL_VIN: J2.1, J3.9
SL_VOL: J2.2, J3.8

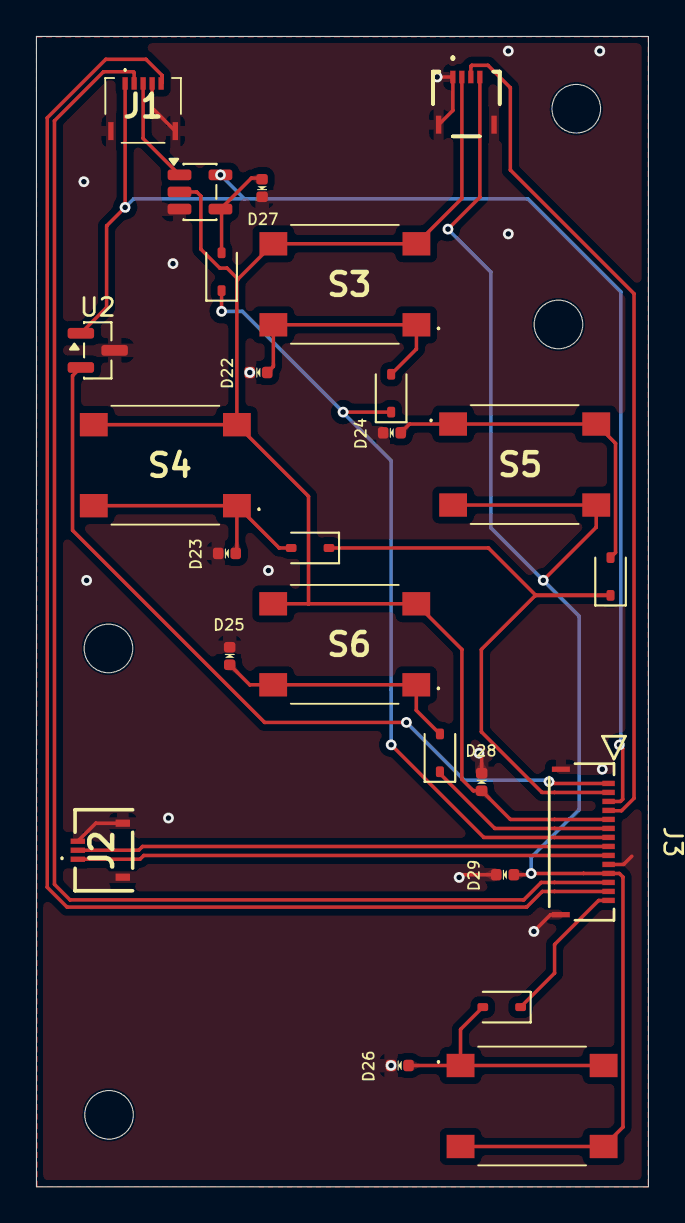
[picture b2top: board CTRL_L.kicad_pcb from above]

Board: 2 copper layers, 34.0 x 63.9 mm, 31 parts (2 on the bottom side), 21 nets.

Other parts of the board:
kibuzzard-6A186FEC: G***; kibuzzard-6A186FEC
kibuzzard-6A187131: G***; kibuzzard-6A187131

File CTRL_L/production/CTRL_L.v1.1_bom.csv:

Designator,Footprint,Quantity,Value,LCSC Part #
"D22, D23, D24, D25, D26, D27, D28, D29",0402,8,ESD5V0B03,C521894
"D3, D4, D5, D6, D7, D8",D_SOD-323,6,1N4148WS,
J2,AYF530365T,1,AYF530365TA,
J3,5034801400,1,5034801400,
J4,5034800440,1,503480-0440,
KIBUZZARD-6A186FEC,kibuzzard-6A186FEC,1,G***,
"S3, S4, S5, S6, S7",B3S1000,5,B3S-1000,
U1,SOT-23-5,1,74LVC1G08,
U2,SOT-23,1,DRV5033FAxDBZ,

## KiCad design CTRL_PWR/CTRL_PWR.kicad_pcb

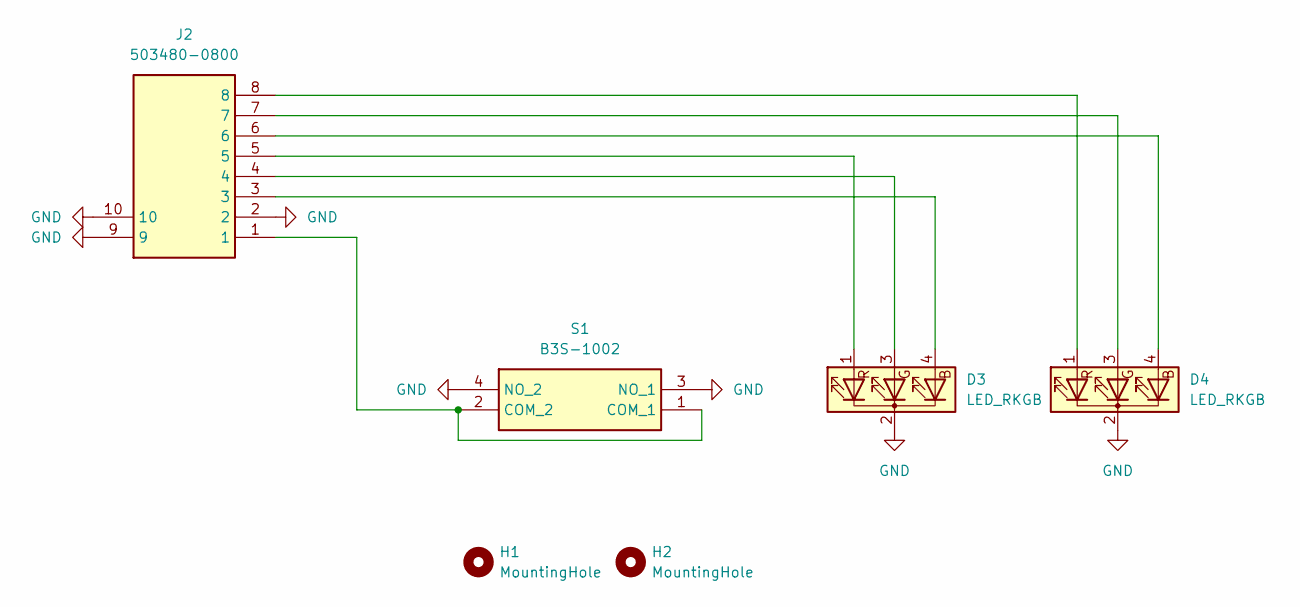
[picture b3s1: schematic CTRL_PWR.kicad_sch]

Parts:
D3, D4: LED_RKGB; LED_D5.0mm-4_RGB; MPN TJ-L5FCMXHTCSLCRGB-A5; LCSC Part C2837020
H1, H2: MountingHole; MountingHole_2.7mm_M2.5; LCSC Part N/A
J2: 503480-0800; 5034800800; Manufacturer_Part_Number 503480-0800
S1: B3S-1002; B3S1002; MPN B3S-1002; LCSC Part C2733654

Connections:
GND: D3.2 (K), D4.2 (K), J2.2, J2.9, J2.10, S1.3 (NO_1), S1.4 (NO_2)
unnamed: D3.4 (BA), J2.3
unnamed: D3.3 (GA), J2.4
unnamed: D3.1 (RA), J2.5
unnamed: D4.4 (BA), J2.6
unnamed: D4.3 (GA), J2.7
unnamed: D4.1 (RA), J2.8
unnamed: J2.1, S1.1 (COM_1), S1.2 (COM_2)

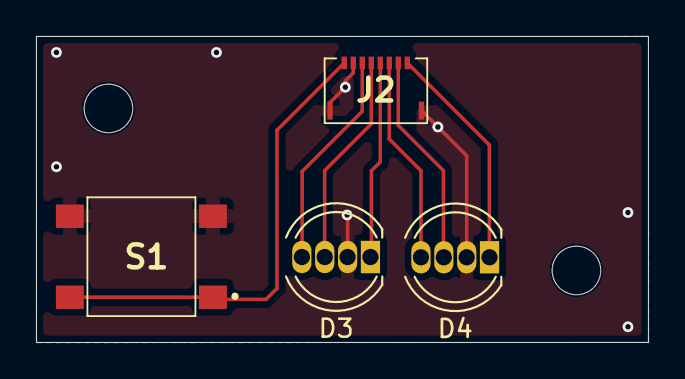
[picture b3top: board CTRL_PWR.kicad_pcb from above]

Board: 2 copper layers, 34.0 x 17.0 mm, 6 parts (0 on the bottom side), 8 nets.

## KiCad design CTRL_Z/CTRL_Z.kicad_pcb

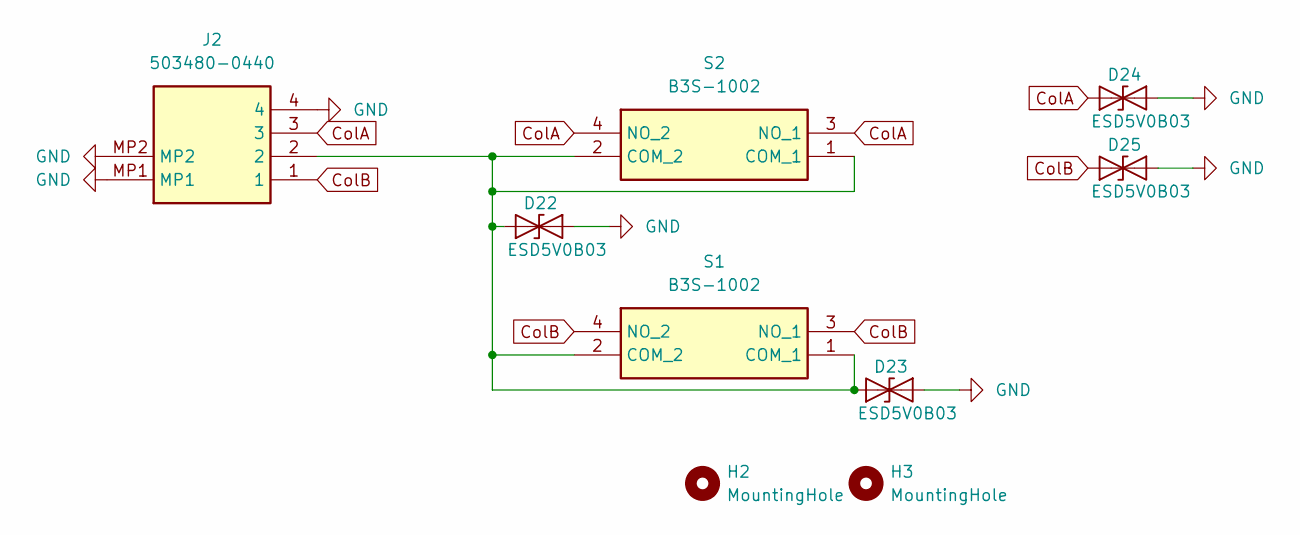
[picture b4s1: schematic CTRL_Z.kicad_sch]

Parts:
D22, D23, D24, D25: ESD5V0B03; D_0402_1005Metric; MPN ESD5V0B03-1006; LCSC Part C521894
H2, H3: MountingHole; MountingHole_2.5mm; LCSC Part N/A
J2: 503480-0440; 5034800440; Mouser Part Number 538-503480-0440
S1, S2: B3S-1002; B3S1002; Mouser Part Number 653-B3S-1002

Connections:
ColA: D24.2 (A2), J2.3, S2.3 (NO_1), S2.4 (NO_2)
ColB: D25.2 (A2), J2.1, S1.3 (NO_1), S1.4 (NO_2)
GND: D22.1 (A1), D23.1 (A1), D24.1 (A1), D25.1 (A1), J2.4, J2.MP1, J2.MP2
unnamed: D22.2 (A2), D23.2 (A2), J2.2, S1.1 (COM_1), S1.2 (COM_2), S2.1 (COM_1), S2.2 (COM_2)
